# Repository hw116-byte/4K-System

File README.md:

# 4K neural recording system

Current design files, datasheet and overview site for the 4K neural recording system.
This repository holds only the latest version of each board. The earlier site
(HowardWHSrun/FPGA_4K) is offline.

- **Website:** https://hw116-byte.github.io/4K-System/
- **Datasheet and user guide:** [datasheet/](https://hw116-byte.github.io/4K-System/datasheet/) (web) or [System_Datasheet_V1.pdf](System_Datasheet_V1.pdf)
- **Direct LDO carrier page:** [direct-ldo/](https://hw116-byte.github.io/4K-System/direct-ldo/)
- **Direct LDO carrier datasheet and programming guide** (XEM8305 pin map, XDC, power-up): [direct-ldo/datasheet/](https://hw116-byte.github.io/4K-System/direct-ldo/datasheet/) · [XDC](direct-ldo/datasheet/Direct_LDO_Carrier_V6_XEM8305.xdc)
- **Boards for fab review (schematic + PCB in the browser):** [fab-review/](https://hw116-byte.github.io/4K-System/fab-review/)
- **KiCad projects and fab files:** [boards/](boards/)
- **24 Nov 2026 overview update:** HDMI Extension Board V41 (male test pins, 12 V fan header), Option B router V3 + LDO board V3 (placement, routing in progress) on 4 of the 8 head stages, G-chip Direct LDO Carrier V6 and the new 4K Direct LDO Carrier V7 (layout placement), printable models set V5, weekly deck [2026-11-25-v9](presentation/meetings/2026-11-25-v9/)
- **25 Nov 2026 weekly deck V11:** adds test-pad slides: Frontend Plan A (V17, frame header) vs Plan B (V18, edge half holes), both with the new 4 × 3 mm flash; FPGA-LDO Plan A (V24) vs Plan B (V26). [Deck](presentation/meetings/2026-11-25-v11/).
- **25 Nov 2026 weekly deck V10:** Option B router V3 routed (layout V1, 6 layers, DRC 0), new schematics for router V3, LDO board V3 and 4K Direct LDO Carrier V7 (schematic V4); LDO board V3 and Carrier V7 routing in progress. [Deck](presentation/meetings/2026-11-25-v10/).

## Boards

**Review page: [Boards for fab review](https://hw116-byte.github.io/4K-System/fab-review/)** opens every board's native KiCad schematic
(all sheets) and PCB in the browser, with the parts list and every file.

`boards/` is a copy of the workspace's Final Versions folder (26 Nov 2026): the latest version of every board with its order files.
Its [START_HERE.md](boards/START_HERE.md) lists versions, order files and open points per board.

| Folder | Board | Version |
|---|---|---|
| [1_HDMI_Extension_Board_V42](boards/1_HDMI_Extension_Board_V42) | HDMI Extension Board | V42 · order_V4 |
| [2_Frontend_FPGA_Board_14_Layers_Plan_A_V19_Plan_B_V20](boards/2_Frontend_FPGA_Board_14_Layers_Plan_A_V19_Plan_B_V20) | Frontend FPGA Board, Test Pad Plan A and Plan B | 14 layers V19 + test frame V9 / V20 + frame V10 |
| [3_FPGA_LDO_Option_A_Plan_A_V24_Plan_B_V26](boards/3_FPGA_LDO_Option_A_Plan_A_V24_Plan_B_V26) | FPGA-LDO PCB Option A, Plan A and Plan B | layout V24 + test frame V4 / V26 + frame V6 |
| [4_ASIC_Boards_V15](boards/4_ASIC_Boards_V15) | ASIC top and bottom boards (PCBWay) | V15 |
| [5_Direct_LDO_Carrier_V6](boards/5_Direct_LDO_Carrier_V6) | G-chip Direct LDO Carrier (built) | V6 |
| [6_Option_B_Router_V3_and_LDO_Board_V3](boards/6_Option_B_Router_V3_and_LDO_Board_V3) | Option B router and LDO board (Plan A and Plan B) | router V3 layout V1 · LDO board V3 layout V6 |
| [7_4K_Direct_LDO_Carrier_V7_Layout_V9](boards/7_4K_Direct_LDO_Carrier_V7_Layout_V9) | 4K Direct LDO Carrier | V7 · layout V9 |
| [8_Frontend_Breakout_Board_V1](boards/8_Frontend_Breakout_Board_V1) | Frontend Breakout Board | V1 · order_V2 |

Each folder has the KiCad project, a schematic PDF, a KiCad ZIP and the
fab/assembly files (Gerbers, BOM, placement). Open the `.kicad_pro` file with
**KiCad 10**; libraries and 3D models are inside each project.

The fab-review pages read the files in `boards/` directly. The overview page's 3D views and card
downloads, the datasheet text and the design review were made against earlier revisions and were not
refreshed in this update.

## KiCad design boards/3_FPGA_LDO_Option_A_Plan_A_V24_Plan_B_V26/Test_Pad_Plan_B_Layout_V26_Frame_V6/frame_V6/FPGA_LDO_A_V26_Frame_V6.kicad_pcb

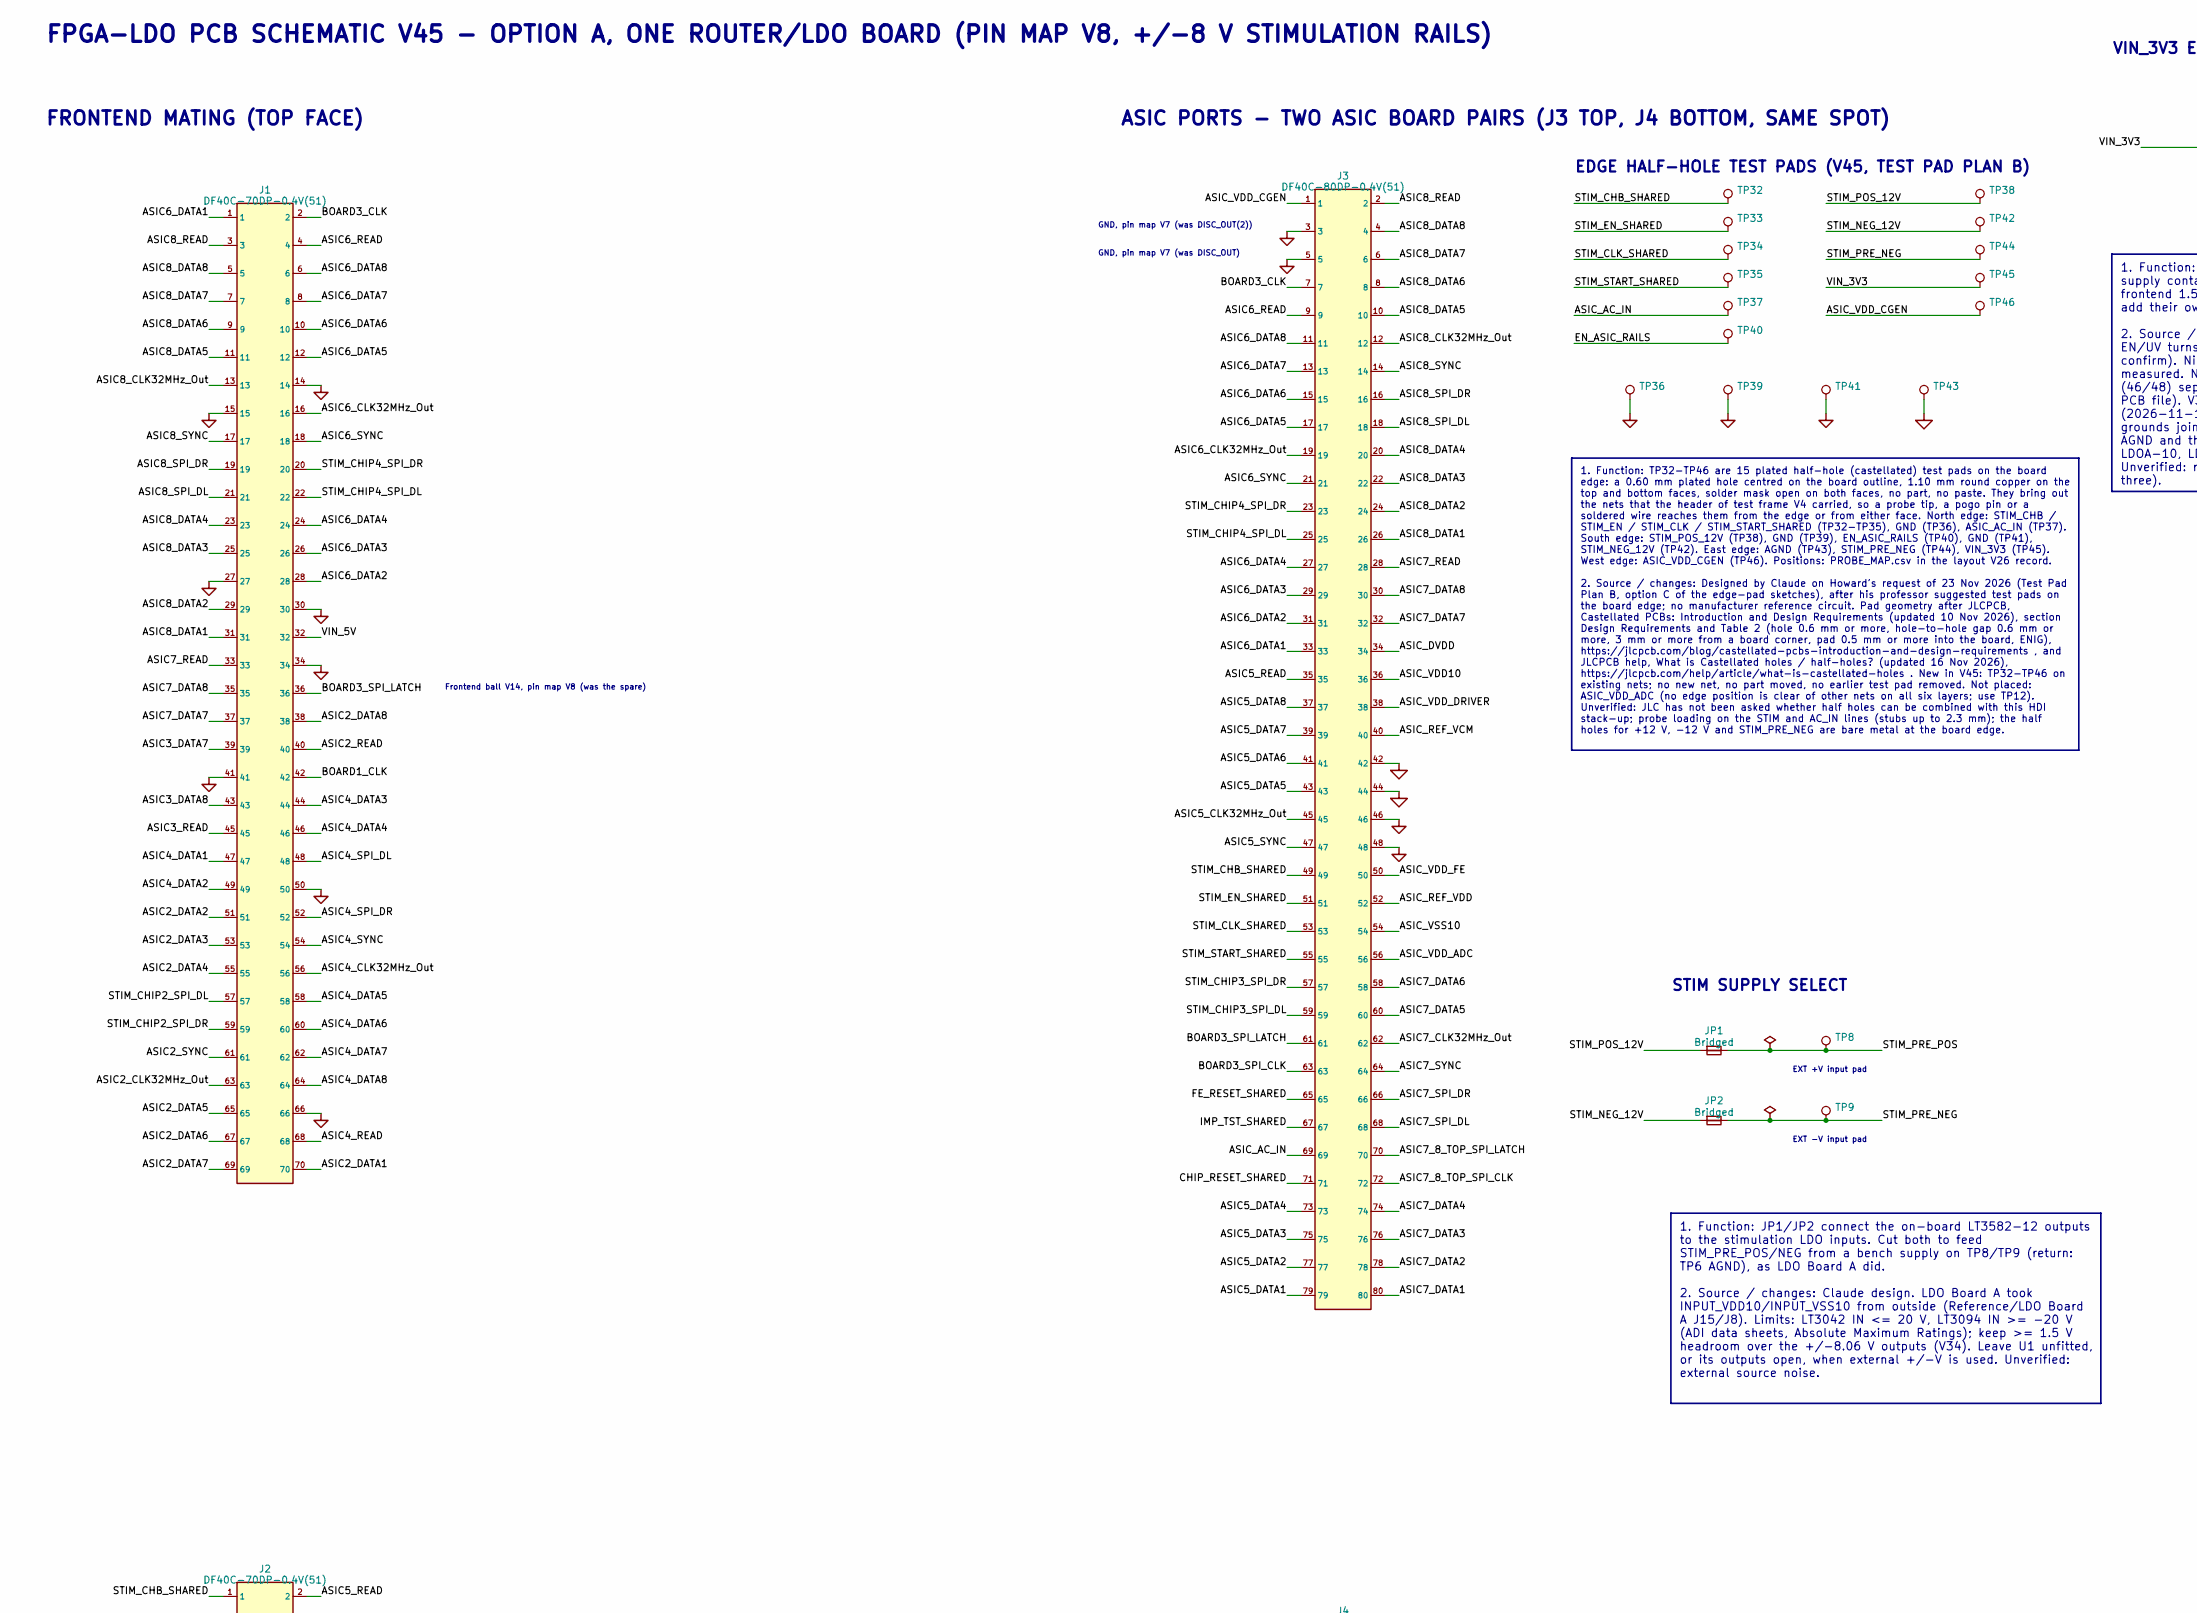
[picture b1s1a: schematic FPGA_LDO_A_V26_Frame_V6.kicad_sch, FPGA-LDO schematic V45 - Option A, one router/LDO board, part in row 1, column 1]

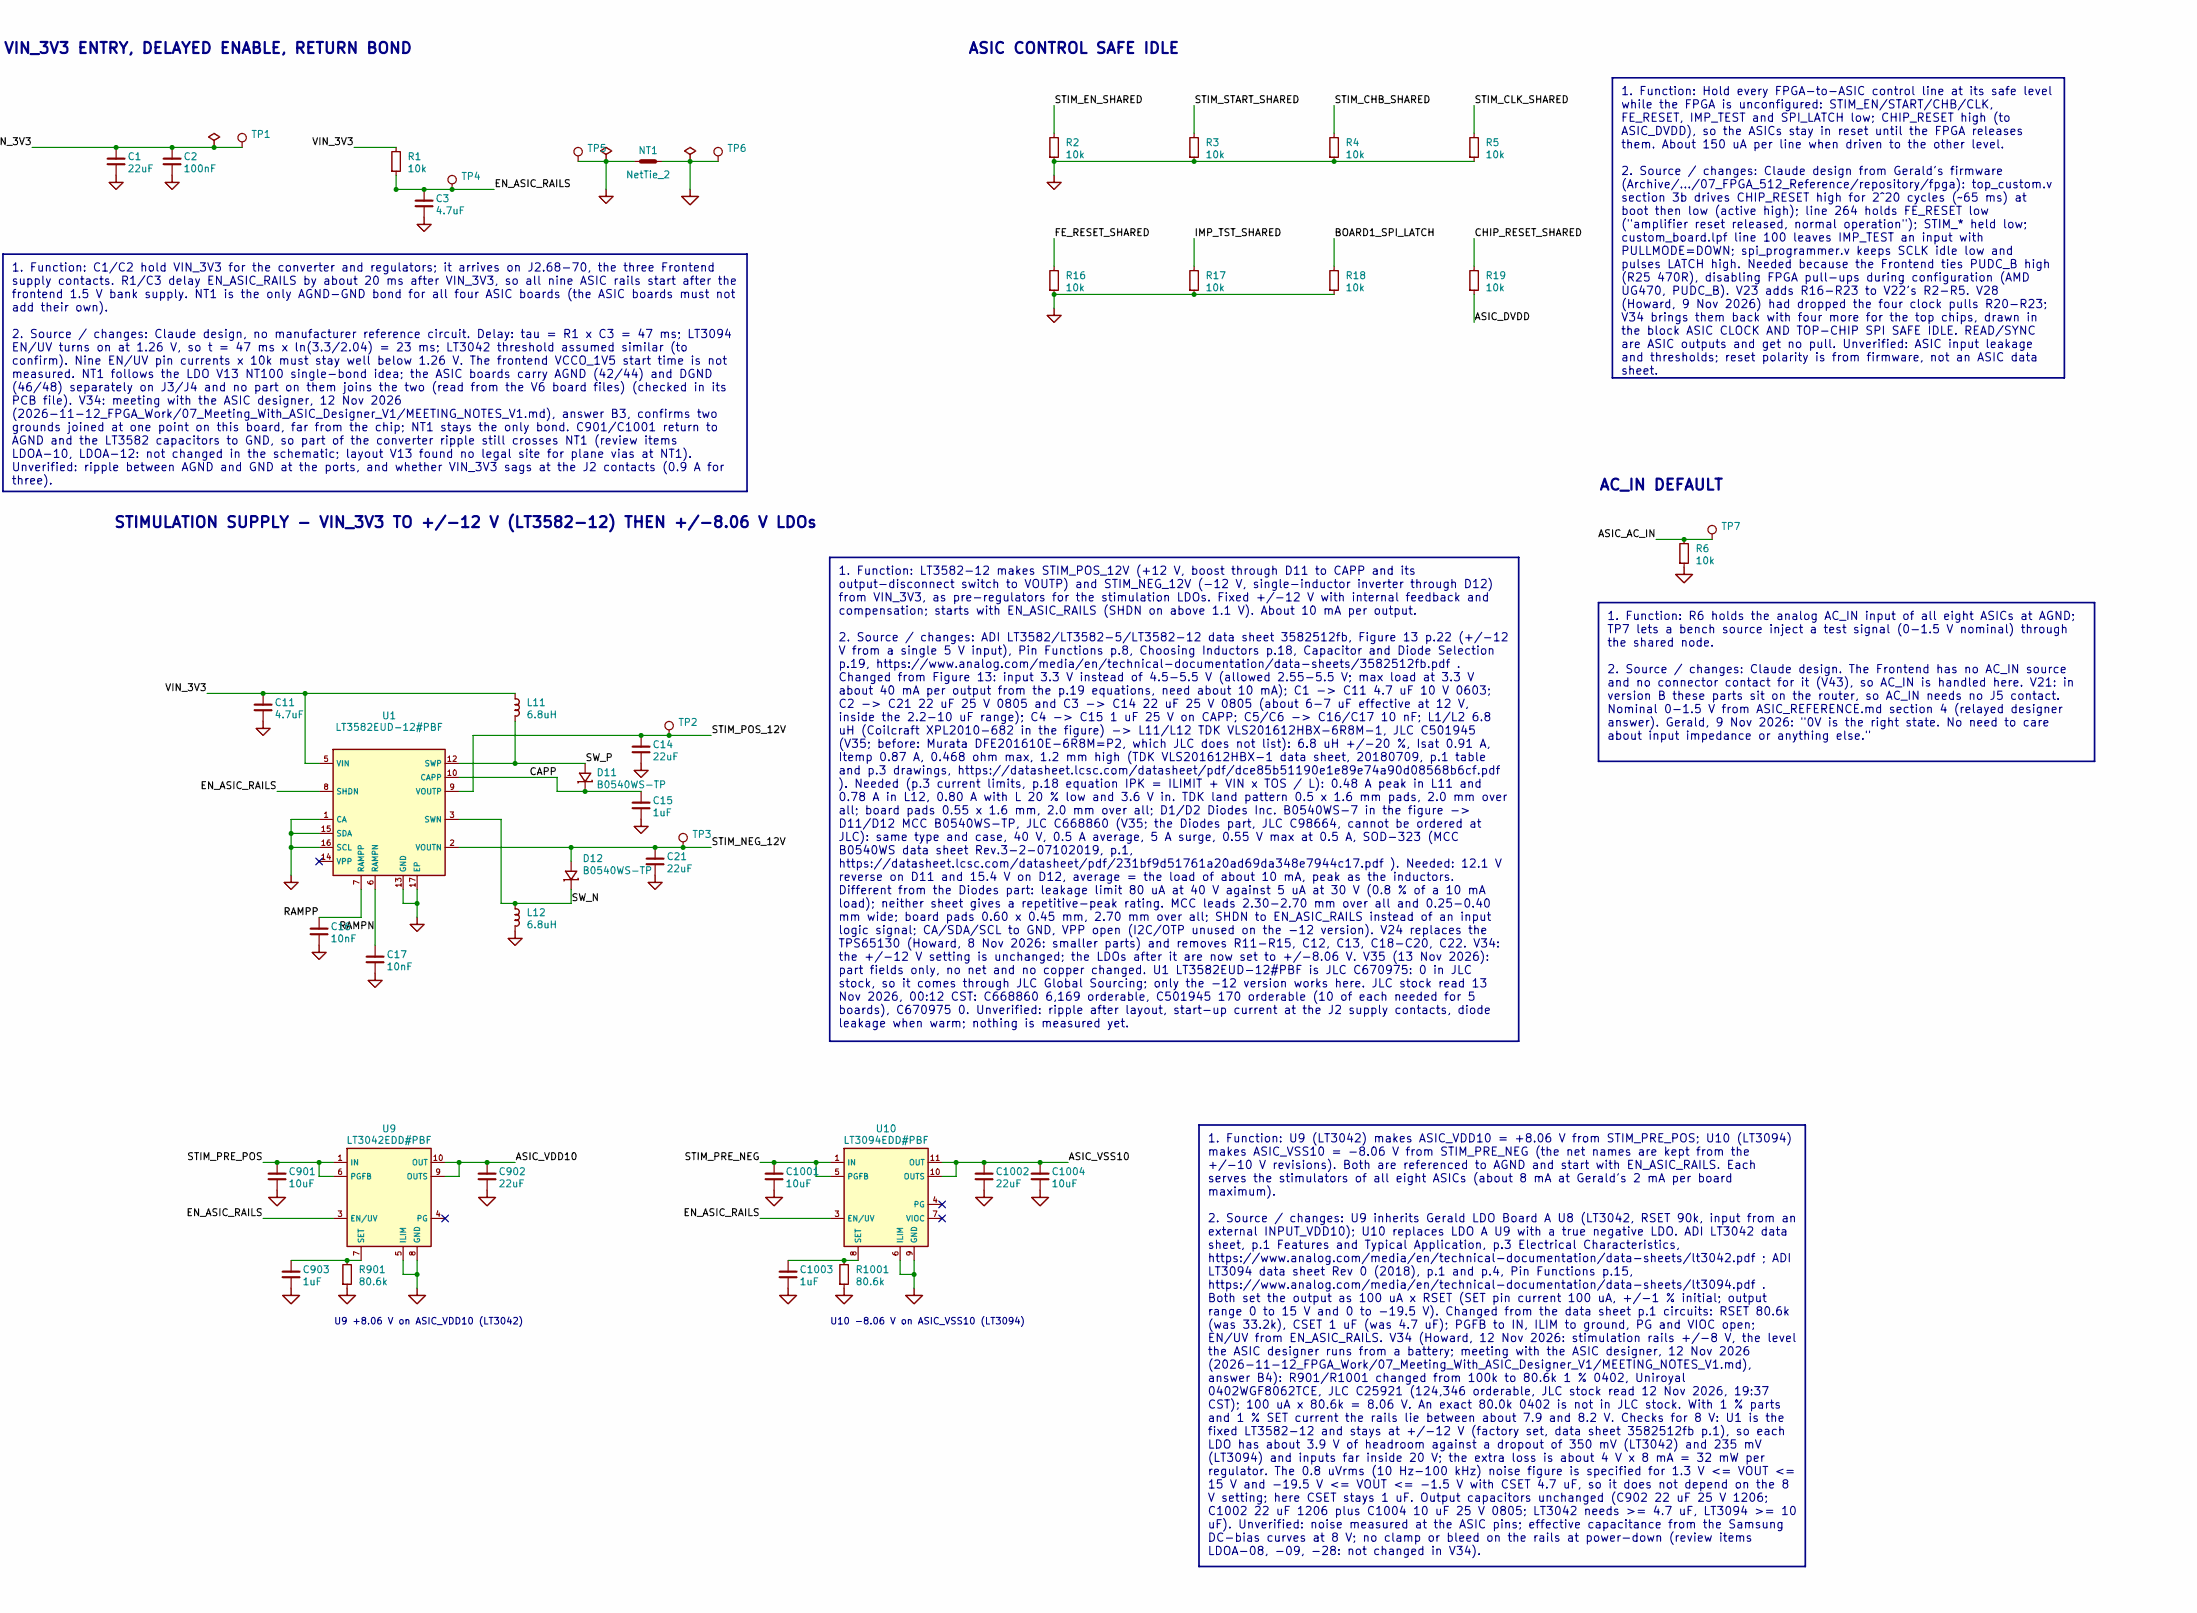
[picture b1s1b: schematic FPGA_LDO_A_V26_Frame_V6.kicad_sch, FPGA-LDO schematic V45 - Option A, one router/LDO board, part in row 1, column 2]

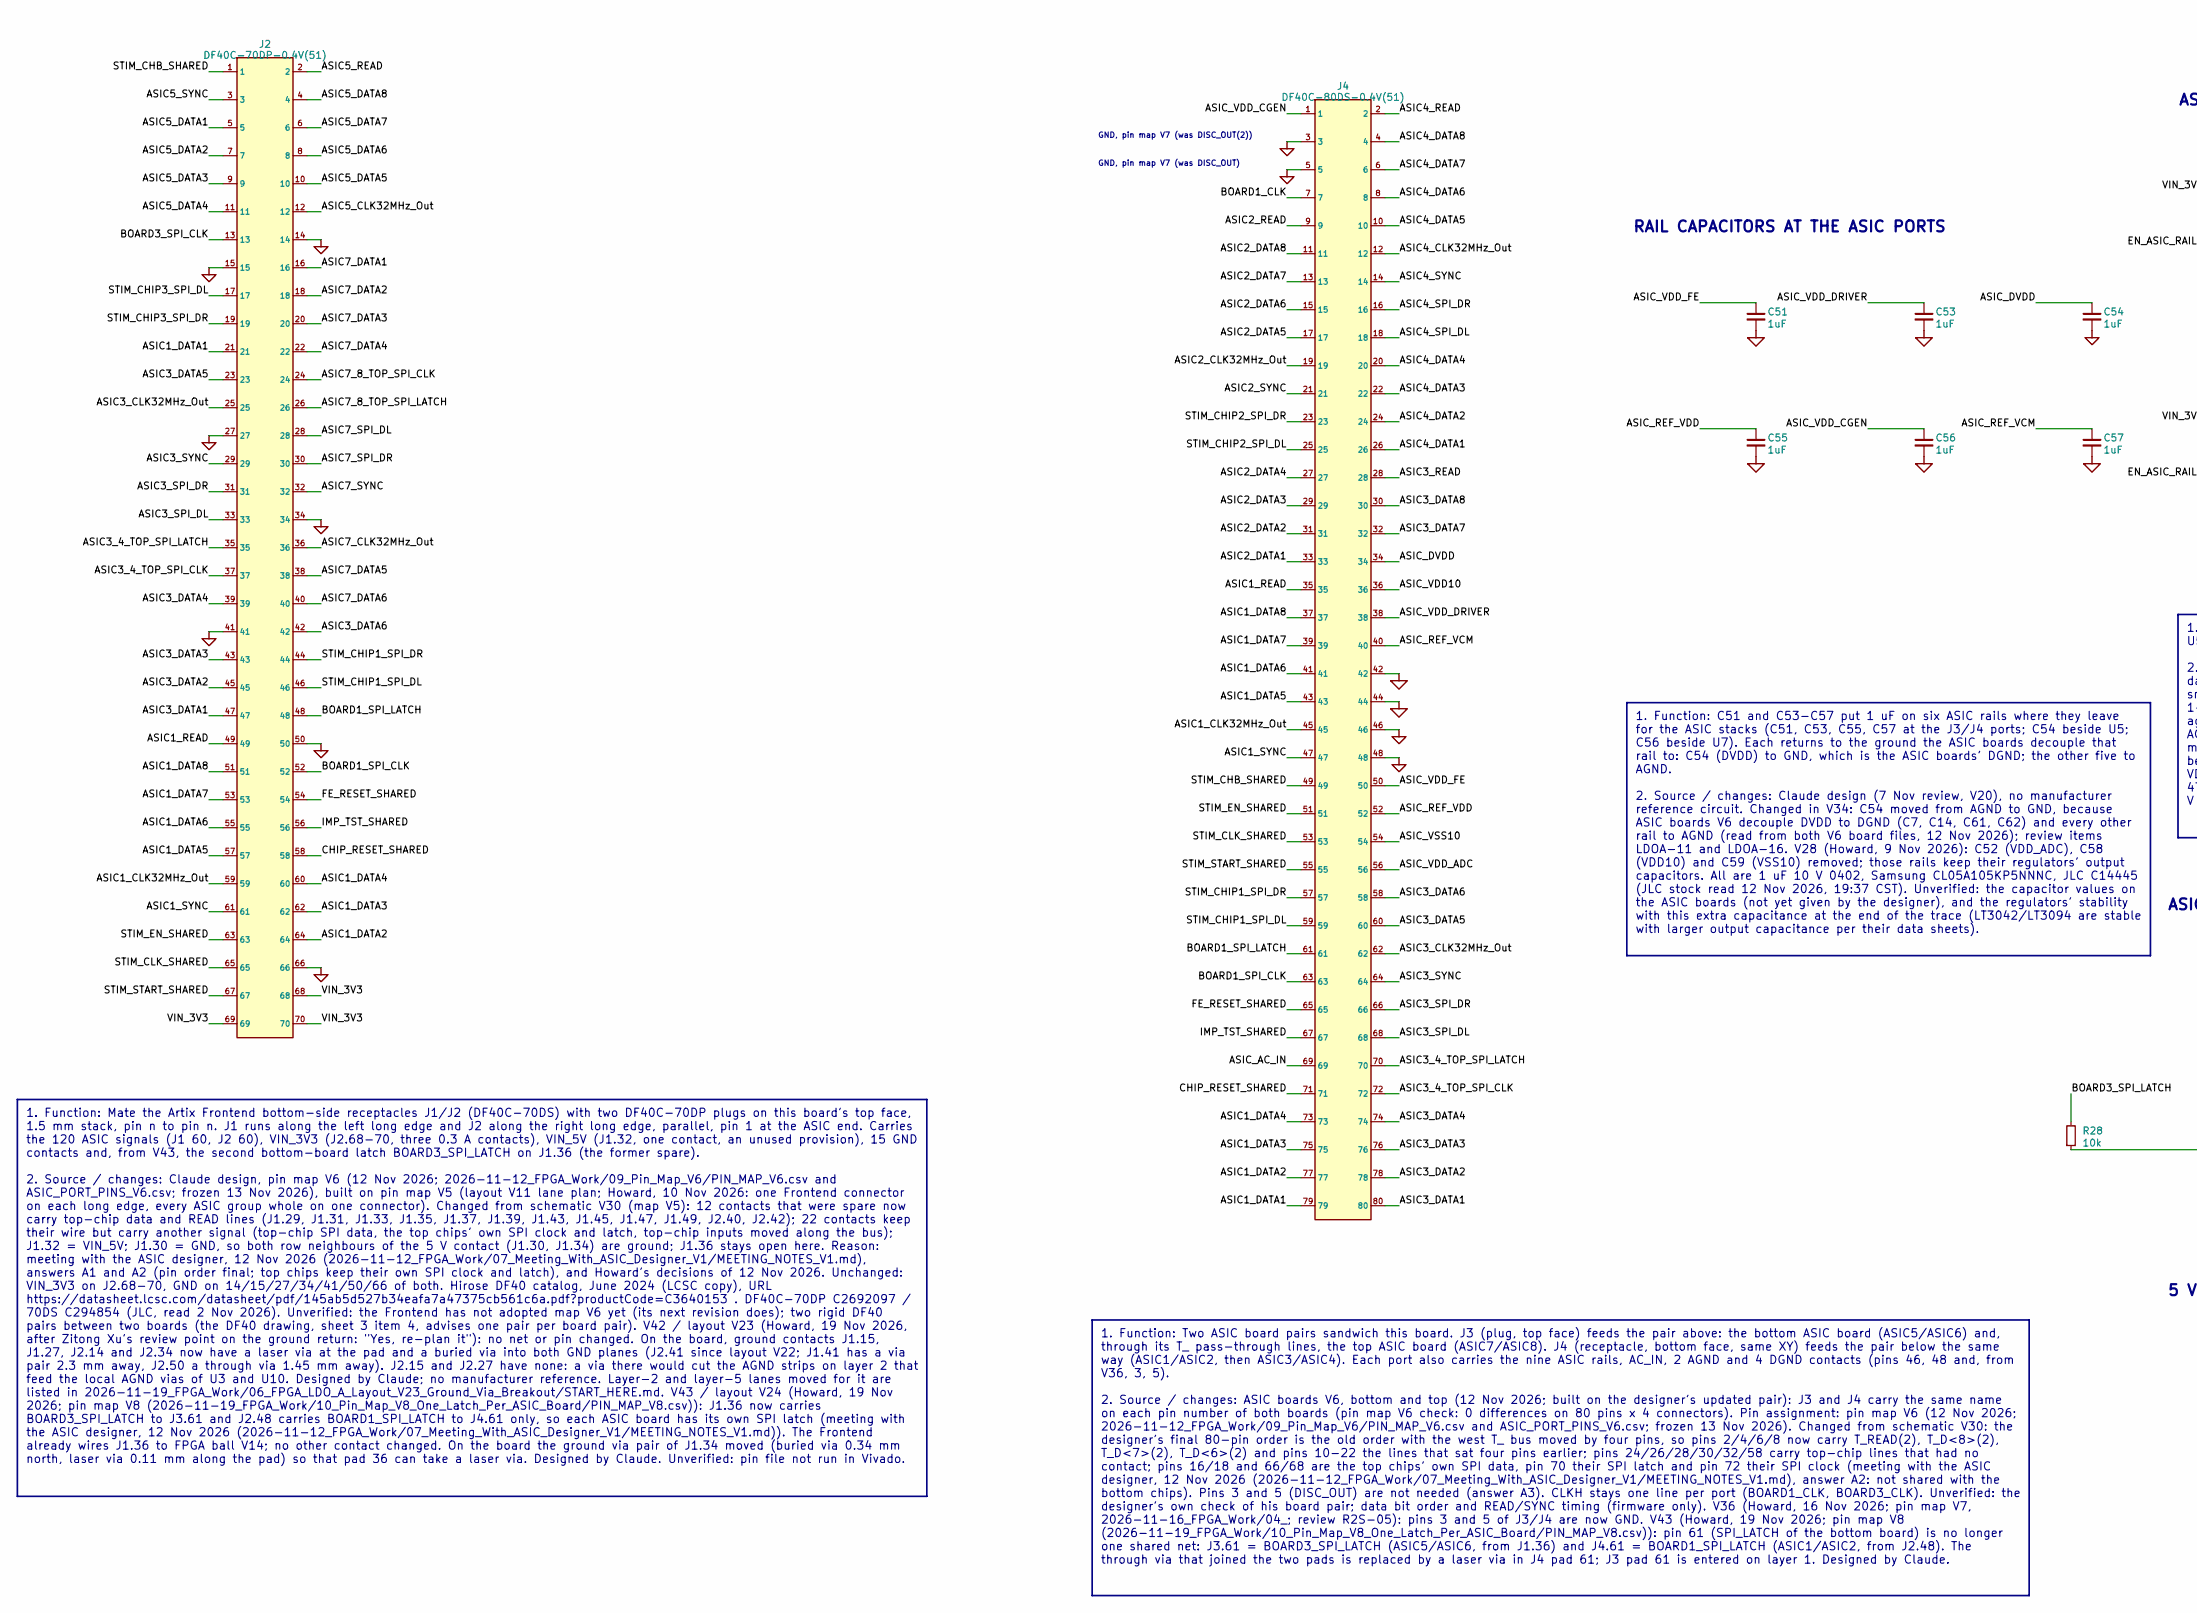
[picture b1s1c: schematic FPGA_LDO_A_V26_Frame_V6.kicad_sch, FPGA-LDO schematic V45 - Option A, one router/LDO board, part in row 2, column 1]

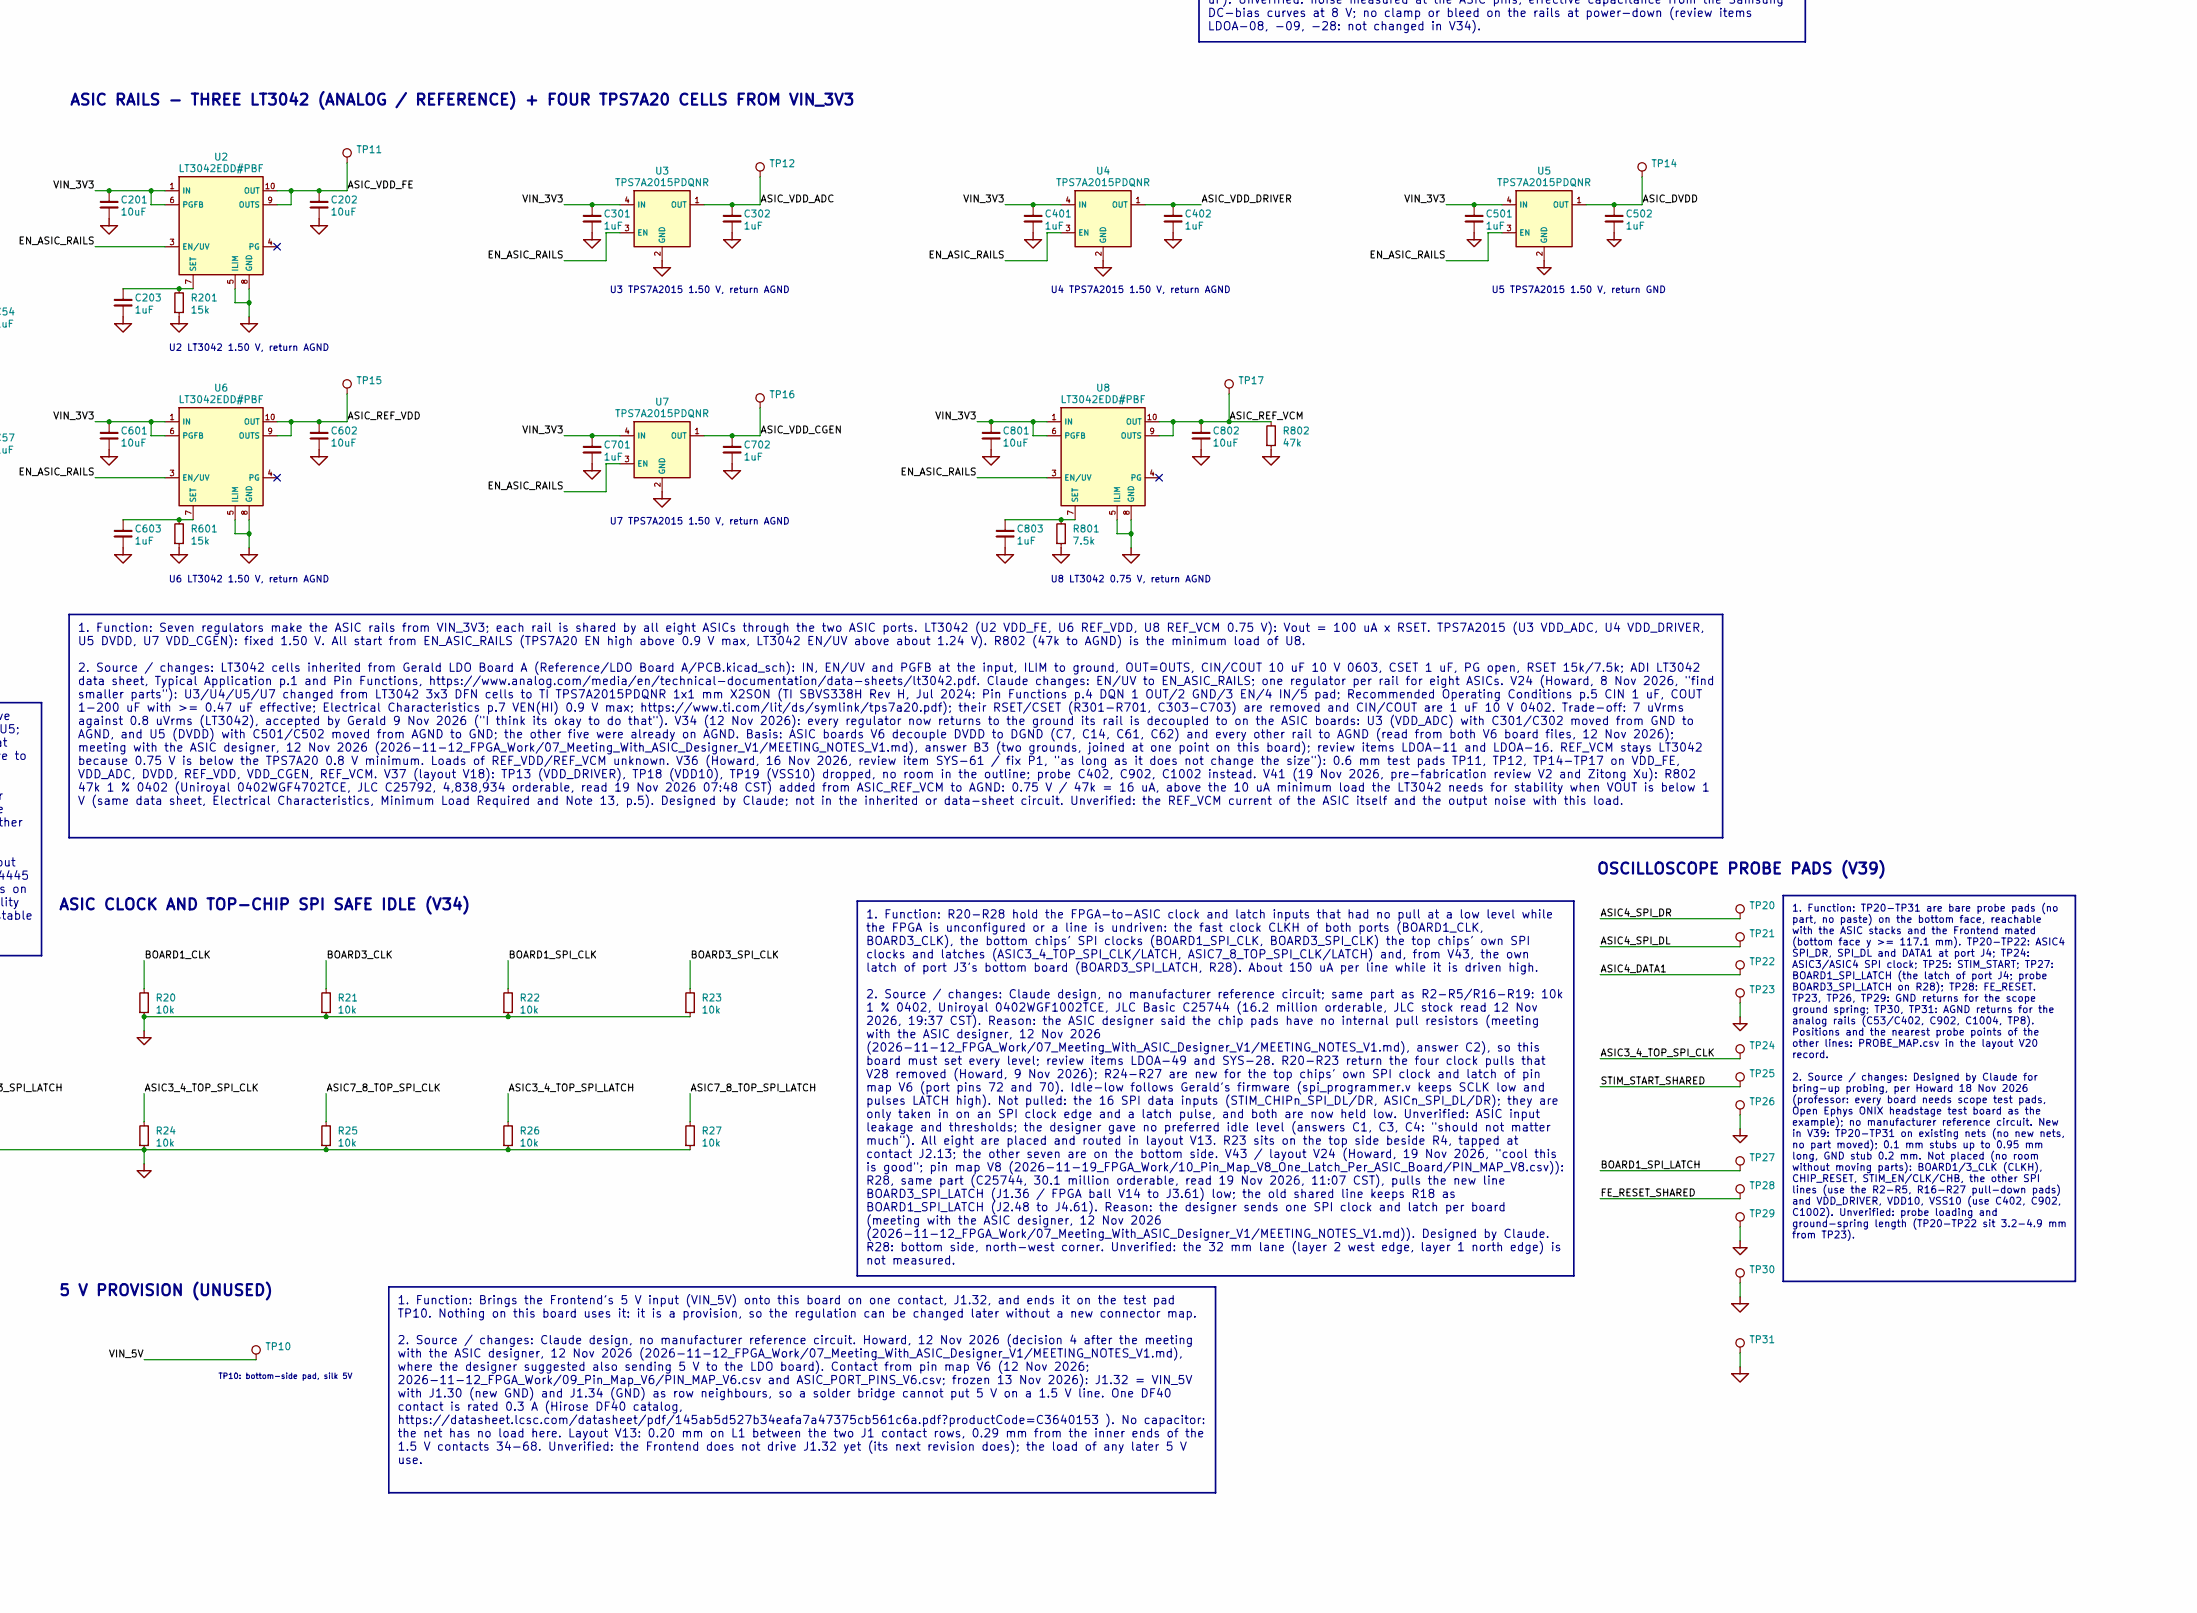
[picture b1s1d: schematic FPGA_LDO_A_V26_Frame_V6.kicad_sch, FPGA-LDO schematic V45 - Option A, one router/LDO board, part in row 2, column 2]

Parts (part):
C1: 22uF; C_0805_2012Metric; Voltage 10V; LCSC C602037
C2: 100nF; C_0402_1005Metric; Voltage 16V; LCSC C307331
C3: 4.7uF; C_0603_1608Metric; Voltage 10V; MPN Samsung CL10A475KP8NNNC (4.7uF 10V X5R 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; LCSC C1705
C11: 4.7uF; C_0603_1608Metric; Voltage 10V; LCSC C1705
C14, C21: 22uF; C_0805_2012Metric; Voltage 25V; MPN Samsung CL21A226MAYNNNE (22uF 25V X5R 0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; LCSC C602037
C15, C903, C1003: 1uF; C_0603_1608Metric; Voltage 25V; MPN Samsung CL10A105KA8NNNC (1uF 25V X5R 06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; LCSC C5673
C16, C17: 10nF; C_0402_1005Metric; Voltage 50V; LCSC C15195
C51, C53, C54, C55, C56, C57, C203, C603, C803: 1uF; C_0402_1005Metric; Voltage 10V; LCSC C14445
C201, C202, C601, C602, C801, C802: 10uF; C_0603_1608Metric; Voltage 10V; MPN Samsung CL10A106KP8NNNC (10uF 10V X5R 0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; LCSC C19702
C301, C302, C401, C402, C501, C502, C701, C702: 1uF; C_0402_1005Metric; Voltage 10V; MPN Samsung CL05A105KP5NNNC (1uF 10V X5R 04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; LCSC C14445
C901, C1001, C1004: 10uF; C_0805_2012Metric; Voltage 25V; MPN Samsung CL21A106KAYNNNE (10uF 25V X5R 0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; LCSC C15850
C902, C1002: 22uF; C_1206_3216Metric; Voltage 25V; MPN Samsung CL31A226KAHNNNE (22uF 25V X5R 1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; LCSC C12891
D11, D12: B0540WS-TP; D_SOD-323; MPN MCC B0540WS-TP (40 V 0.5 A SOD-323); LCSC C668860
J1, J2: DF40C-70DP-0.4V(51); Hirose_DF40C-70DP-0.4V_2x35-1MP_P0.4mm; MPN DF40C-70DP-0.4V(51); LCSC C2692097
J3: DF40C-80DP-0.4V(51); Hirose_DF40C-80DP-0.4V_2x40-1MP_P0.4mm; MPN DF40C-80DP-0.4V(51); LCSC C294544
J4: DF40C-80DS-0.4V(51); Hirose_DF40C-80DS-0.4V_2x40_P0.4mm; MPN DF40C-80DS-0.4V(51); LCSC C312960
JP1, JP2: Bridged; SolderJumper-2_P1.3mm_Bridged_RoundedPad1.0x1.5mm
L11, L12: 6.8uH; L_Murata_DFE201610P; MPN TDK VLS201612HBX-6R8M-1 (6.8 uH 20 %, 2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; LCSC C501945
NT1: NetTie_2; NetTie-2_SMD_Pad0.5mm
R1, R2, R3, R4, R5, R6, R16, R17, R18, R19: 10k; R_0402_1005Metric; Tolerance 1%; LCSC C25744
R20, R21, R22, R23, R24, R25, R26, R27, R28: 10k; R_0402_1005Metric; Tolerance 1%; MPN Uniroyal 0402WGF1002TCE (10k 1% 0402); LCSC C25744
R201, R601: 15k; R_0402_1005Metric; Tolerance 1%; LCSC C25756
R801: 7.5k; R_0402_1005Metric; Tolerance 1%; LCSC C25918
R802: 47k; R_0402_1005Metric; Tolerance 1%; MPN Uniroyal 0402WGF4702TCE (47k 1% 0402); LCSC C25792
R901, R1001: 80.6k; R_0402_1005Metric; Tolerance 1%; MPN Uniroyal 0402WGF8062TCE (80.6k 1% 0402); LCSC C25921
TP1: VIN_3V3; TestPoint_Pad_D1.0mm_Compact
TP2: STIM_POS_12V; TestPoint_Pad_D1.0mm_Compact
TP3: STIM_NEG_12V; TestPoint_Pad_D1.0mm_Compact
TP4: EN_ASIC_RAILS; TestPoint_Pad_D1.0mm_Compact
TP5: GND; TestPoint_Pad_D1.0mm_Compact
TP6: AGND; TestPoint_Pad_D1.0mm_Compact
TP7: ASIC_AC_IN; TestPoint_Pad_D1.0mm_Compact
TP8: STIM_PRE_POS; TestPoint_Pad_D1.0mm_Compact
TP9: STIM_PRE_NEG; TestPoint_Pad_D1.0mm_Compact
TP10: VIN_5V; TestPoint_Pad_D1.0mm_Compact
TP11: ASIC_VDD_FE; TestPoint_Pad_D0.6mm_Compact
TP12: ASIC_VDD_ADC; TestPoint_Pad_D0.6mm_Compact
TP14: ASIC_DVDD; TestPoint_Pad_D0.6mm_Compact
TP15: ASIC_REF_VDD; TestPoint_Pad_D0.6mm_Compact
TP16: ASIC_VDD_CGEN; TestPoint_Pad_D0.6mm_Compact
TP17: ASIC_REF_VCM; TestPoint_Pad_D0.6mm_Compact
TP20: ASIC4_SPI_DR; TestPoint_Pad_D0.6mm_Compact
TP21: ASIC4_SPI_DL; TestPoint_Pad_D0.6mm_Compact
TP22: ASIC4_DATA1; TestPoint_Pad_D0.8mm_Compact015
TP23: GND; TestPoint_Pad_D1.0mm_Compact015
TP24: ASIC3_4_TOP_SPI_CLK; TestPoint_Pad_D0.8mm_Compact015
TP25: STIM_START_SHARED; TestPoint_Pad_D0.6mm_Compact
TP26: GND; TestPoint_Pad_D0.6mm_Compact
TP27: BOARD1_SPI_LATCH; TestPoint_Pad_D0.6mm_Compact
TP28: FE_RESET_SHARED; TestPoint_Pad_D0.6mm_Compact
TP29: GND; TestPoint_Pad_D0.8mm_Compact015
TP30, TP31: AGND; TestPoint_Pad_D0.8mm_Compact015
TP32: STIM_CHB_SHARED; TestPoint_HalfHole_D0.6mm_Pad1.1mm
TP33: STIM_EN_SHARED; TestPoint_HalfHole_D0.6mm_Pad1.1mm
TP34: STIM_CLK_SHARED; TestPoint_HalfHole_D0.6mm_Pad1.1mm
TP35: STIM_START_SHARED; TestPoint_HalfHole_D0.6mm_Pad1.1mm
TP36, TP39, TP41: GND; TestPoint_HalfHole_D0.6mm_Pad1.1mm
TP37: ASIC_AC_IN; TestPoint_HalfHole_D0.6mm_Pad1.1mm
TP38: STIM_POS_12V; TestPoint_HalfHole_D0.6mm_Pad1.1mm
TP40: EN_ASIC_RAILS; TestPoint_HalfHole_D0.6mm_Pad1.1mm
TP42: STIM_NEG_12V; TestPoint_HalfHole_D0.6mm_Pad1.1mm
TP43: AGND; TestPoint_HalfHole_D0.6mm_Pad1.1mm
TP44: STIM_PRE_NEG; TestPoint_HalfHole_D0.6mm_Pad1.1mm
TP45: VIN_3V3; TestPoint_HalfHole_D0.6mm_Pad1.1mm
TP46: ASIC_VDD_CGEN; TestPoint_HalfHole_D0.6mm_Pad1.1mm
U1: LT3582EUD-12#PBF; QFN-16-1EP_3x3mm_P0.5mm_EP1.45x1.45mm; MPN LT3582EUD-12#PBF; LCSC C670975
U2, U6, U8, U9: LT3042EDD#PBF; DFN-10-1EP_3x3mm_P0.5mm_EP1.65x2.38mm; MPN LT3042EDD#PBF; LCSC C580010
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
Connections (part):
/ASIC1_CLK32MHz_Out: J2.59, J4.45
/ASIC1_DATA1: J2.21, J4.79
/ASIC1_DATA2: J2.64, J4.77
/ASIC1_DATA3: J2.62, J4.75
/ASIC1_DATA4: J2.60, J4.73
/ASIC1_DATA5: J2.57, J4.43
/ASIC1_DATA6: J2.55, J4.41
/ASIC1_DATA7: J2.53, J4.39
/ASIC1_DATA8: J2.51, J4.37
/ASIC1_READ: J2.49, J4.35
/ASIC1_SYNC: J2.61, J4.47
/ASIC2_CLK32MHz_Out: J1.63, J4.19
/ASIC2_DATA1: J1.70, J4.33
/ASIC2_DATA2: J1.51, J4.31
/ASIC2_DATA3: J1.53, J4.29
/ASIC2_DATA4: J1.55, J4.27
/ASIC2_DATA5: J1.65, J4.17
/ASIC2_DATA6: J1.67, J4.15
/ASIC2_DATA7: J1.69, J4.13
/ASIC2_DATA8: J1.38, J4.11
/ASIC2_READ: J1.40, J4.9
/ASIC2_SYNC: J1.61, J4.21
/ASIC3_4_TOP_SPI_CLK: J2.37, J4.72, R24.1, TP24.1
/ASIC3_4_TOP_SPI_LATCH: J2.35, J4.70, R26.1
/ASIC3_CLK32MHz_Out: J2.25, J4.62
/ASIC3_DATA1: J2.47, J4.80
/ASIC3_DATA2: J2.45, J4.78
/ASIC3_DATA3: J2.43, J4.76
/ASIC3_DATA4: J2.39, J4.74
/ASIC3_DATA5: J2.23, J4.60
/ASIC3_DATA6: J2.42, J4.58
/ASIC3_DATA7: J1.39, J4.32
/ASIC3_DATA8: J1.43, J4.30
/ASIC3_READ: J1.45, J4.28
/ASIC3_SPI_DL: J2.33, J4.68
/ASIC3_SPI_DR: J2.31, J4.66
/ASIC3_SYNC: J2.29, J4.64
/ASIC4_CLK32MHz_Out: J1.56, J4.12
/ASIC4_DATA1: J1.47, J4.26, TP22.1
/ASIC4_DATA2: J1.49, J4.24
/ASIC4_DATA3: J1.44, J4.22
/ASIC4_DATA4: J1.46, J4.20
/ASIC4_DATA5: J1.58, J4.10
/ASIC4_DATA6: J1.60, J4.8
/ASIC4_DATA7: J1.62, J4.6
/ASIC4_DATA8: J1.64, J4.4
/ASIC4_READ: J1.68, J4.2
/ASIC4_SPI_DL: J1.48, J4.18, TP21.1
/ASIC4_SPI_DR: J1.52, J4.16, TP20.1
/ASIC4_SYNC: J1.54, J4.14
/ASIC5_CLK32MHz_Out: J2.12, J3.45
/ASIC5_DATA1: J2.5, J3.79
/ASIC5_DATA2: J2.7, J3.77
/ASIC5_DATA3: J2.9, J3.75
/ASIC5_DATA4: J2.11, J3.73
/ASIC5_DATA5: J2.10, J3.43
/ASIC5_DATA6: J2.8, J3.41
/ASIC5_DATA7: J2.6, J3.39
/ASIC5_DATA8: J2.4, J3.37
/ASIC5_READ: J2.2, J3.35
/ASIC5_SYNC: J2.3, J3.47
/ASIC6_CLK32MHz_Out: J1.16, J3.19
/ASIC6_DATA1: J1.1, J3.33
/ASIC6_DATA2: J1.28, J3.31
/ASIC6_DATA3: J1.26, J3.29
/ASIC6_DATA4: J1.24, J3.27
/ASIC6_DATA5: J1.12, J3.17
/ASIC6_DATA6: J1.10, J3.15
/ASIC6_DATA7: J1.8, J3.13
/ASIC6_DATA8: J1.6, J3.11
/ASIC6_READ: J1.4, J3.9
/ASIC6_SYNC: J1.18, J3.21
/ASIC7_8_TOP_SPI_CLK: J2.24, J3.72, R25.1
/ASIC7_8_TOP_SPI_LATCH: J2.26, J3.70, R27.1
/ASIC7_CLK32MHz_Out: J2.36, J3.62
/ASIC7_DATA1: J2.16, J3.80
/ASIC7_DATA2: J2.18, J3.78
/ASIC7_DATA3: J2.20, J3.76
/ASIC7_DATA4: J2.22, J3.74
/ASIC7_DATA5: J2.38, J3.60
/ASIC7_DATA6: J2.40, J3.58
/ASIC7_DATA7: J1.37, J3.32
/ASIC7_DATA8: J1.35, J3.30
/ASIC7_READ: J1.33, J3.28
/ASIC7_SPI_DL: J2.28, J3.68
/ASIC7_SPI_DR: J2.30, J3.66
/ASIC7_SYNC: J2.32, J3.64
/ASIC8_CLK32MHz_Out: J1.13, J3.12
/ASIC8_DATA1: J1.31, J3.26
/ASIC8_DATA2: J1.29, J3.24
/ASIC8_DATA3: J1.25, J3.22
/ASIC8_DATA4: J1.23, J3.20
/ASIC8_DATA5: J1.11, J3.10
/ASIC8_DATA6: J1.9, J3.8
/ASIC8_DATA7: J1.7, J3.6
/ASIC8_DATA8: J1.5, J3.4
/ASIC8_READ: J1.3, J3.2
/ASIC8_SPI_DL: J1.21, J3.18
/ASIC8_SPI_DR: J1.19, J3.16
/ASIC8_SYNC: J1.17, J3.14
/ASIC_AC_IN: J3.69, J4.69, R6.1, TP7.1, TP37.1
/ASIC_DVDD: C54.1, C502.1, J3.34, J4.34, R19.2, TP14.1, U5.1 (OUT)
/ASIC_REF_VCM: C57.1, C802.1, J3.40, J4.40, R802.1, TP17.1, U8.9 (OUTS), U8.10 (OUT)
/ASIC_REF_VDD: C55.1, C602.1, J3.52, J4.52, TP15.1, U6.9 (OUTS), U6.10 (OUT)
/ASIC_VDD10: C902.1, J3.36, J4.36, U9.9 (OUTS), U9.10 (OUT)
/ASIC_VDD_ADC: C302.1, J3.56, J4.56, TP12.1, U3.1 (OUT)
/ASIC_VDD_CGEN: C56.1, C702.1, J3.1, J4.1, TP16.1, TP46.1, U7.1 (OUT)
/ASIC_VDD_DRIVER: C53.1, C402.1, J3.38, J4.38, U4.1 (OUT)
/ASIC_VDD_FE: C51.1, C202.1, J3.50, J4.50, TP11.1, U2.9 (OUTS), U2.10 (OUT)
/ASIC_VSS10: C1002.1, C1004.1, J3.54, J4.54, U10.10 (OUTS), U10.11 (OUT), U10.12 (OUT)
/BOARD1_CLK: J1.42, J4.7, R20.1
/BOARD1_SPI_CLK: J2.52, J4.63, R22.1
/BOARD1_SPI_LATCH: J2.48, J4.61, R18.1, TP27.1
/BOARD3_CLK: J1.2, J3.7, R21.1
/BOARD3_SPI_CLK: J2.13, J3.63, R23.1
/BOARD3_SPI_LATCH: J1.36, J3.61, R28.1
/CAPP: C15.1, D11.1 (K), U1.10 (CAPP), U1.11 (CAPP)
/CHIP_RESET_SHARED: J2.58, J3.71, J4.71, R19.1
/EN_ASIC_RAILS: C3.1, R1.2, TP4.1, TP40.1, U1.8 (SHDN), U2.3 (EN/UV), U3.3 (EN), U4.3 (EN), U5.3 (EN), U6.3 (EN/UV), U7.3 (EN), U8.3 (EN/UV), U9.3 (EN/UV), U10.3 (EN/UV)
/FE_RESET_SHARED: J2.54, J3.65, J4.65, R16.1, TP28.1
/IMP_TST_SHARED: J2.56, J3.67, J4.67, R17.1
/RAMPN: C17.1, U1.6 (RAMPN)
/RAMPP: C16.1, U1.7 (RAMPP)
/STIM_CHB_SHARED: J2.1, J3.49, J4.49, R4.1, TP32.1
/STIM_CHIP1_SPI_DL: J2.46, J4.59
/STIM_CHIP1_SPI_DR: J2.44, J4.57
/STIM_CHIP2_SPI_DL: J1.57, J4.25
/STIM_CHIP2_SPI_DR: J1.59, J4.23
/STIM_CHIP3_SPI_DL: J2.17, J3.59
/STIM_CHIP3_SPI_DR: J2.19, J3.57
/STIM_CHIP4_SPI_DL: J1.22, J3.25
/STIM_CHIP4_SPI_DR: J1.20, J3.23
/STIM_CLK_SHARED: J2.65, J3.53, J4.53, R5.1, TP34.1
/STIM_EN_SHARED: J2.63, J3.51, J4.51, R2.1, TP33.1
/STIM_NEG_12V: C21.1, D12.2 (A), JP2.1, TP3.1, TP42.1, U1.2 (VOUTN)
/STIM_POS_12V: C14.1, JP1.1, TP2.1, TP38.1, U1.9 (VOUTP)
/STIM_PRE_NEG: C1001.1, JP2.2, TP9.1, TP44.1, U10.1 (IN), U10.2 (IN), U10.5 (PGFB), U10.13 (IN)
/STIM_PRE_POS: C901.1, JP1.2, TP8.1, U9.1 (IN), U9.2 (IN), U9.6 (PGFB)
/STIM_START_SHARED: J2.67, J3.55, J4.55, R3.1, TP25.1, TP35.1
/SW_N: D12.1 (K), L12.1, U1.3 (SWN), U1.4 (SWN)
/SW_P: D11.2 (A), L11.2, U1.12 (SWP)
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
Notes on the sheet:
FPGA-LDO PCB SCHEMATIC V45 - OPTION A, ONE ROUTER/LDO BOARD (PIN MAP V8, +/-8 V STIMULATION RAILS)
RAIL CAPACITORS AT THE ASIC PORTS
1. Function: C51 and C53-C57 put 1 uF on six ASIC rails where they leave for the ASIC stacks (C51, C53, C55, C57 at the J3/J4 ports; C54 beside U5; C56 beside U7). Each returns to the ground the ASIC boards decouple that rail to: C54 (DVDD) to GND, which is the ASIC boards' DGND; the other five to 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
Frontend ball V14, pin map V8 (was the spare)
FRONTEND MATING (TOP FACE)
1. Function: Mate the Artix Frontend bottom-side receptacles J1/J2 (DF40C-70DS) with two DF40C-70DP plugs on this board's top face, 1.5 mm stack, pin n to pin n. J1 runs along the left long edge and J2 along the right long edge, parallel, pin 1 at the ASIC end. Carries the 120 ASIC signals (J1 60, 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
GND, pin map V7 (was DISC_OUT(2))
GND, pin map V7 (was DISC_OUT)
ASIC PORTS - TWO ASIC BOARD PAIRS (J3 TOP, J4 BOTTOM, SAME SPOT)
1. Function: Two ASIC board pairs sandwich this board. J3 (plug, top face) feeds the pair above: the bottom ASIC board (ASIC5/ASIC6) and, through its T_ pass-through lines, the top ASIC board (ASIC7/ASIC8). J4 (receptacle, bottom face, same XY) feeds the pair below the same way (ASIC1/ASIC2, then A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
ASIC RAILS - THREE LT3042 (ANALOG / REFERENCE) + FOUR TPS7A20 CELLS FROM VIN_3V3
U2 LT3042 1.50 V, return AGND
U3 TPS7A2015 1.50 V, return AGND
U4 TPS7A2015 1.50 V, return AGND
U5 TPS7A2015 1.50 V, return GND
U6 LT3042 1.50 V, return AGND
U7 TPS7A2015 1.50 V, return AGND
U8 LT3042 0.75 V, return AGND
1. Function: Seven regulators make the ASIC rails from VIN_3V3; each rail is shared by all eight ASICs through the two ASIC ports. LT3042 (U2 VDD_FE, U6 REF_VDD, U8 REF_VCM 0.75 V): Vout = 100 uA x RSET. TPS7A2015 (U3 VDD_ADC, U4 VDD_DRIVER, U5 DVDD, U7 VDD_CGEN): fixed 1.50 V. All start from EN_AS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
STIMULATION SUPPLY - VIN_3V3 TO +/-12 V (LT3582-12) THEN +/-8.06 V LDOs
1. Function: LT3582-12 makes STIM_POS_12V (+12 V, boost through D11 to CAPP and its output-disconnect switch to VOUTP) and STIM_NEG_12V (-12 V, single-inductor inverter through D12) from VIN_3V3, as pre-regulators for the stimulation LDOs. Fixed +/-12 V with internal feedback and compensation; star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
U9 +8.06 V on ASIC_VDD10 (LT3042)
U10 -8.06 V on ASIC_VSS10 (LT3094)
1. Function: U9 (LT3042) makes ASIC_VDD10 = +8.06 V from STIM_PRE_POS; U10 (LT3094) makes ASIC_VSS10 = -8.06 V from STIM_PRE_NEG (the net names are kept from the +/-10 V revisions). Both are referenced to AGND and start with EN_ASIC_RAILS. Each serves the stimulators of all eight ASICs (about 8 mA 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
STIM SUPPLY SELECT
EXT +V input pad
EXT -V input pad
1. Function: JP1/JP2 connect the on-board LT3582-12 outputs to the stimulation LDO inputs. Cut both to feed STIM_PRE_POS/NEG from a bench supply on TP8/TP9 (return: TP6 AGND), as LDO Board A did. 2. Source / changes: Claude design. LDO Board A took INPUT_VDD10/INPUT_VSS10 from outside (Reference/LD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
VIN_3V3 ENTRY, DELAYED ENABLE, RETURN BOND
1. Function: C1/C2 hold VIN_3V3 for the converter and regulators; it arrives on J2.68-70, the three Frontend supply contacts. R1/C3 delay EN_ASIC_RAILS by about 20 ms after VIN_3V3, so all nine ASIC rails start after the frontend 1.5 V bank supply. NT1 is the only AGND-GND bond for all four ASIC bo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
ASIC CONTROL SAFE IDLE
1. Function: Hold every FPGA-to-ASIC control line at its safe level while the FPGA is unconfigured: STIM_EN/START/CHB/CLK, FE_RESET, IMP_TEST and SPI_LATCH low; CHIP_RESET high (to ASIC_DVDD), so the ASICs stay in reset until the FPGA releases them. About 150 uA per line when driven to the other le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
AC_IN DEFAULT
1. Function: R6 holds the analog AC_IN input of all eight ASICs at AGND; TP7 lets a bench source inject a test signal (0-1.5 V nominal) through the shared node. 2. Source / changes: Claude design. The Frontend has no AC_IN source and no connector contact for it (V43), so AC_IN is handled here. V21: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
ASIC CLOCK AND TOP-CHIP SPI SAFE IDLE (V34)
1. Function: R20-R28 hold the FPGA-to-ASIC clock and latch inputs that had no pull at a low level while the FPGA is unconfigured or a line is undriven: the fast clock CLKH of both ports (BOARD1_CLK, BOARD3_CLK), the bottom chips' SPI clocks (BOARD1_SPI_CLK, BOARD3_SPI_CLK) the top chips' own SPI cl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
5 V PROVISION (UNUSED)
TP10: bottom-side pad, silk 5V
1. Function: Brings the Frontend's 5 V input (VIN_5V) onto this board on one contact, J1.32, and ends it on the test pad TP10. Nothing on this board uses it: it is a provision, so the regulation can be changed later without a new connector map. 2. Source / changes: Claude design, no manufacturer re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
OSCILLOSCOPE PROBE PADS (V39)
